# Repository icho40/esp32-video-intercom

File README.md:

# ESP32 Open Intercom

Lokale Video-Türsprechanlage für drei Parteien: Eine Türstation mit zwei ESP32-S3-Boards versorgt Android-Tablets mit Klingelmeldung, Livebild und Audio. Gegensprechen erfolgt über eine gedrückt gehaltene Sprechtaste. Für den Betrieb wird keine Cloud benötigt.

## Aufbau

**Beide ESP32-Boards sitzen zusammen mit der Steuerplatine im Gehäuse der Türstation.**

- **Seeed XIAO ESP32-S3 Sense:** erfasst Kamerabilder und Mikrofonton. Bild und Ton gehen über UART mit 2 Mbit/s zum Waveshare. Mikrofonaufnahme und Versand sind getrennt; Audio wird beim Senden bevorzugt.
- **Waveshare ESP32-S3 DevKit:** liest die drei Klingeltaster, verwaltet Ruf und Gespräch, überträgt die Daten im WLAN und empfängt die Sprache vom Tablet.
- **MAX98357A und Lautsprecher:** geben den vom Tablet gesendeten Ton an der Türstation aus. Der Rückweg läuft direkt vom Waveshare über I²S zum Verstärker.
- **Gemeinsame Steuerplatine:** verbindet die Komponenten und versorgt beide Boards über ihren 5-V/GND-Eingang.
- **Android-App auf drei Fire-Tablets:** P1 = Erdgeschoss, P2 = 1. Stock, P3 = Keller. Jedes Tablet reagiert auf seine zugewiesene Klingeltaste und verwendet seinen eigenen Klingelton. Fully Single App Kiosk übernimmt den Kioskbetrieb.

Ein Router beziehungsweise Access Point verbindet Türstation und Innenstationen. Die aktuellen Innenstationen verwenden die native Android-App; die älteren Browser-Oberflächen im Repository sind historische Entwicklungsstände.

## Funktionen

| Funktion | Stand |
|---|---|
| Drei Klingeltaster mit Zuordnung P1/P2/P3 | Implementiert |
| Livebild und Audio von der Türstation | Implementiert und bereits praktisch betrieben |
| Gegensprechen per Sprechtaste, Ende-Taste | In der Tablet-App implementiert und praktisch geprüft |
| Unbeantworteter Ruf endet nach 30 Sekunden | Implementiert |
| Gesprächsfreigabe nach Verbindungsabbruch | Implementiert |
| Eigene Klingeltöne und Etagenanzeige | Implementiert; P3 heißt Keller |
| Tablet-Autostart, Home-Sperre und Mikrofonfreigabe | Mit Fully eingerichtet und nach Neustart geprüft |
| WLAN-Empfangsanzeige über Zahnrad | Implementiert auf allen drei Tablets, ohne PIN |
| Gemeinsamer WLAN-Wechsel von Tablet und Türstation | Implementiert, mit Rückfall bei fehlender Bestätigung |
| RSSI-Anzeige und WLAN-Diagnoseseite | Implementiert |
| Firmware-Update des Waveshare über WLAN | Implementiert und am Gerät geprüft |
| Separate Handy-App für P1 im selben WLAN | Testversion; Sprechtastenprüfung noch offen |

**Aktuell offene Punkte:** Im zuletzt dokumentierten Standorttest vom 25.10.2026 bestand erneut eine Störung beim Kamera-/Audioempfang über UART. Die Diagnose zeigt diese an, behebt sie aber nicht. Ein erfolgreicher vollständiger Audio-/Videotest nach diesem Standortwechsel ist noch nicht dokumentiert. Die Handy-Testversion ist ebenfalls noch nicht abschließend freigegeben.

MQTT, Home Assistant und Türöffnersteuerung gehören nicht zum derzeit bestätigten Funktionsumfang.

## Gebrauchsanleitung

[Druckbare Anleitung als PDF](docs/Gebrauchsanleitung.pdf) · [Admin-Fassung mit Lautstärke](docs/Gebrauchsanleitung-Admin.pdf) | [Bearbeitbare Textfassung](docs/Gebrauchsanleitung.md) | Handy-Apps installieren: [PDF](docs/Handy-App-Installation.pdf) · [Text](docs/Handy-App-Installation.md)

## Bedienung

1. Klingeltaster P1, P2 oder P3 an der Türstation drücken.
2. Das zugewiesene Tablet klingelt und zeigt das Kamerabild.
3. **Sprechen gedrückt halten:** nimmt den Ruf an und aktiviert das Tablet-Mikrofon. Währenddessen ist die Wiedergabe der Türstation am Tablet stumm.
4. **Loslassen:** beendet die Mikrofonübertragung; der Ton der Türstation wird wieder hörbar.
5. **Ende:** beendet den Ruf. Ohne Annahme läuft er nach 30 Sekunden ab.

Bei der Einrichtung die Mikrofonabfrage **direkt am Tablet mit „Bei Nutzung der App“ bestätigen**. Eine ausschließlich über USB gesetzte Freigabe ersetzt diesen Schritt im bewährten Ablauf nicht.

## WLAN und Wartung

An jedem Tablet: **Zahnrad rechts oben antippen** öffnet direkt die **WLAN-Empfangsanzeige** der Türstation mit Signal, IP und Diagnoseseite. Seit 06.11.2026 ohne PIN und ohne Menüpunkt zum Ändern des WLANs.

Neue WLAN-Zugangsdaten bekommt die Station über ihr Einrichtungs-WLAN: Ist sie 60 Sekunden ohne WLAN, öffnet sie „OpenIntercom-Setup“ selbst. Mit einem Handy verbinden und http://192.168.4.1 öffnen. Hängt sie in einem WLAN, das die Tablets nicht erreichen, hilft nur ein Neustart mit Netzwahl (P1 = Test-WLAN, P2 = Haus-WLAN) oder USB; eine Haltegeste an P1 gibt es seit 06.11.2026 nicht mehr. Zugangsdaten werden auf der Station gespeichert; die aktuelle Firmware enthält kein fest eingebautes privates WLAN als Rückfall.

- Diagnose im lokalen Netz: http://STATIONS-IP/diagnose
- JSON-Diagnose: http://STATIONS-IP/api/diagnose
- Waveshare-Update: http://STATIONS-IP/update, mit Administrator-Anmeldung und Sitzungstoken
- OTA aktualisiert die Waveshare-Firmware; die XIAO wird separat per USB programmiert.

Details zu Freigaben, WLAN-Wechsel, Wiederherstellung und OTA: [WLAN-Einrichtung und Wartung](docs/wlan-einrichtung.md).

## Quellcode

| Verzeichnis | Zweck |
|---|---|
| firmware/doorstation_v2 | Aktuelle Waveshare-Firmware |
| firmware/xiao_cam/xiao_video_uart | XIAO: Kamera, Mikrofon und UART |
| android | Tablet-App |
| android-phone | Handy-Apps, je eine pro Klingel (P1–P3) |
| hardware/aussenstation | KiCad-Unterlagen der Steuerplatine |
| tools | Wartungswerkzeuge, unter anderem gedrosselter OTA-Upload |

Weitere technische Details: [Architektur](docs/ARCHITECTURE.md), [Stand 17.10.2026](docs/stand-2026-10-17.md), [Tablet-Bildausrichtung 24.10.2026](docs/stand-2026-10-24.md). Datierte Dokumente halten den jeweiligen damaligen Prüfstand fest.

## Bauen

Tablet-App im Verzeichnis android:

    ./gradlew :app:assembleDebug

Handy-Testversion im Verzeichnis android-phone:

    ./gradlew :app:assembleDebug

Waveshare mit Arduino CLI:

    arduino-cli compile --fqbn esp32:esp32:esp32s3:FlashSize=8M,PartitionScheme=default_8MB,PSRAM=opi,CDCOnBoot=default firmware/doorstation_v2

Die erforderlichen Arduino-Bibliotheken und das ESP32-Boardpaket müssen installiert sein. Für USB-Wiederherstellung nach OTA den aktiven Firmware-Slot berücksichtigen; nicht blind nur app0 überschreiben.

## Eigene Anpassungen

Diese öffentliche Fassung enthält keine Zugangsdaten und keine Medien Dritter. Vor dem Einsatz anpassen:

- **WLAN-Namen:** In `firmware/doorstation_v2/Config.h` stehen die Namen der beiden WLANs (`HOME_WIFI_SSID`, `TEST_WIFI_SSID`). Das Firmware-Update ist nur im `HOME_WIFI_SSID` erlaubt. Die Zugangsdaten selbst kommen über das Einrichtungs-WLAN in die Station.
- **Admin-Passwort** für `/update`, `/audio` und `/ansage`: per USB mit `OTA_SET_PASSWORD <passwort>` setzen. In der Anleitung steht dafür der Platzhalter ‹Admin-Passwort›.
- **Klingeltöne:** `tools/make_ringtones.py` erzeugt einfache, freie Töne (`res/raw/klingel_p1.mp3` … `p3`). Eigene Töne unter gleichem Namen ersetzen.
- **Logo:** optional. Eine eigene PNG-Datei als `android/app/src/main/res/drawable-nodpi/wg_logo.png` ablegen, dann erscheint sie im Kopf der PDF-Anleitung. In den Apps ist kein Logo eingebaut.
- **Platzhalter** wie `[Seriennr. Tablet 1]` oder `XX:XX:XX:XX:XX:XX` in den datierten Stand-Dokumenten stehen für die Geräte der ursprünglichen Installation.

Fertige Firmware und APKs gibt es unter **Releases**.

**Sprachaufnahmen:** Die beiden voreingestellten Ansagesätze (`Sprache/nicht_da_andere_etage.mp3`, `Sprache/nicht_zuhause_auf_dem_handy_erreichbar.mp3`, eingebaut in `firmware/doorstation_v2/DefaultAnnouncements.h`) wurden mit ElevenLabs im bezahlten Starter-Tarif erzeugt, der die kommerzielle Nutzung erlaubt. Wer eigene Sätze verwenden will, ersetzt die Dateien und führt `tools/make_default_announcements.py` aus oder lädt Sätze über die Seite `/ansage` hoch.

## Projektstatus und Lizenz

Eigenbauprojekt, seit November 2026 an einem Haus mit drei Parteien in Betrieb. Die dokumentierten Tests unterscheiden zwischen bereits bestätigten Funktionen und noch offenen Prüfungen. Private WLAN-Zugangsdaten, PINs, OTA-Passwörter und Geräteabbilder gehören nicht ins Repository.

GPL-3.0-or-later, siehe [Lizenz](LICENSE).

Dokumentation aktualisiert am 23.11.2026.

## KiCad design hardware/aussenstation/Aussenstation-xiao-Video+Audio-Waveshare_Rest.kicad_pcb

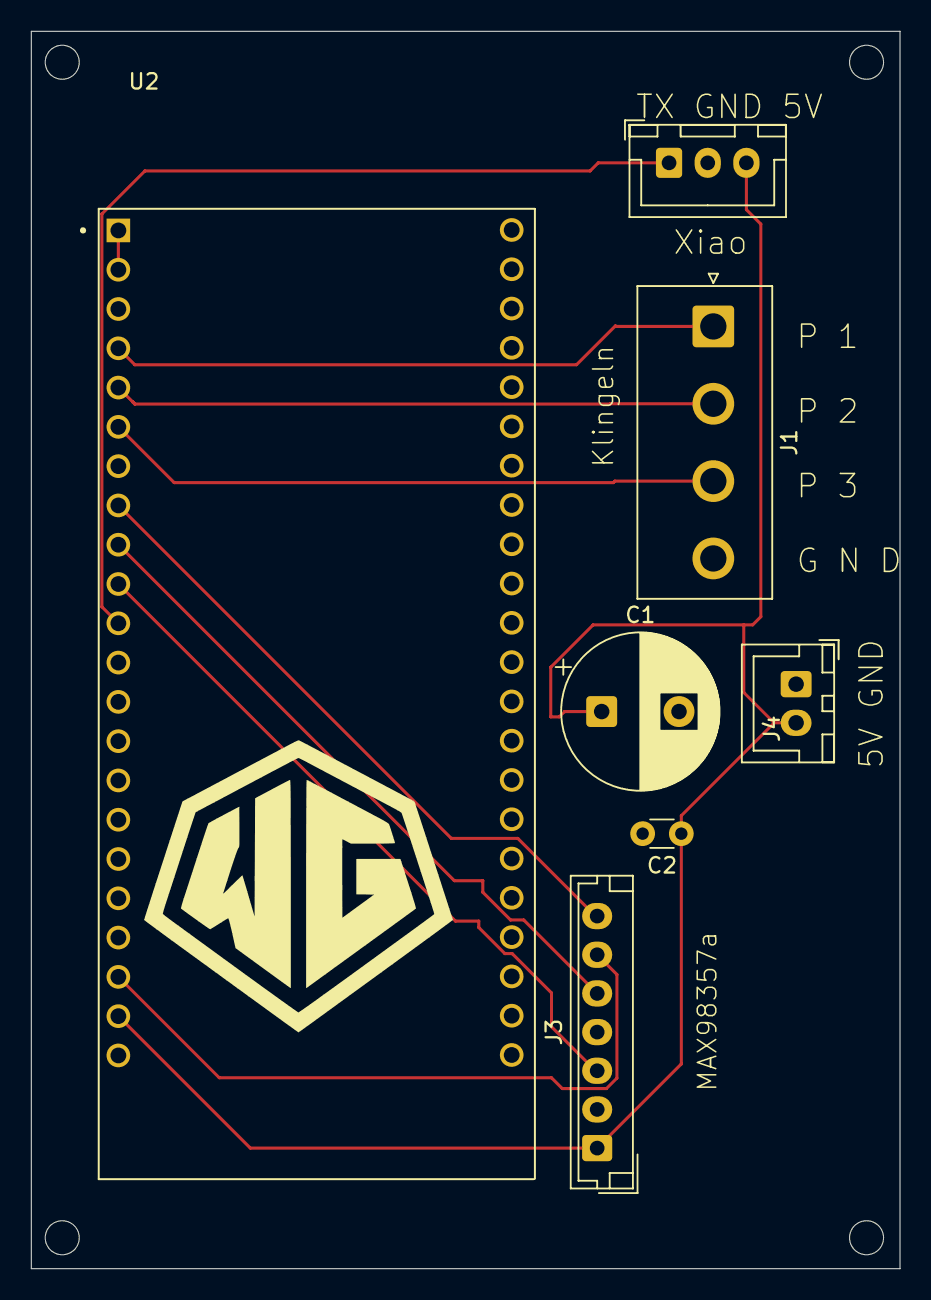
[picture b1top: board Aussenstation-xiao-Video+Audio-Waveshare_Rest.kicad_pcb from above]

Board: 2 copper layers, 56.2 x 80.0 mm, 7 parts (0 on the bottom side), 11 nets.

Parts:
C1: C_Polarized_Small; CP_Radial_D10.0mm_P5.00mm
C2: C_Small; C_Disc_D3.0mm_W1.6mm_P2.50mm
J1: Klingeln; JST_NV_B04P-NV_1x04_P5.00mm_Vertical
J2: Anschluß Xiao; JST_XH_B3B-XH-A_1x03_P2.50mm_Vertical
J3: MAX98357a; JST_EH_B7B-EH-A_1x07_P2.50mm_Vertical
J4: 5V; JST_XH_B2B-XH-A_1x02_P2.50mm_Vertical
U2: ESP32-S3-DEVKITC-1-N8R2; XCVR_ESP32-S3-DEVKITC-1-N8R2

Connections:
3V3: U2.J1_1 (3V3), U2.J1_2 (3V3)
GND: C1.2, C2.2, J1.4, J2.2, J3.2, J4.1 (GND), U2.J1_22 (GND), U2.J3_1 (GND), U2.J3_21 (GND), U2.J3_22 (GND)
unnamed: J1.1, U2.J1_4 (GPIO4)
unnamed: J1.2, U2.J1_5 (GPIO5)
unnamed: J1.3, U2.J1_6 (GPIO6)
unnamed: J2.1, U2.J1_11 (GPIO18)
unnamed: C1.1, C2.1, J2.3, J3.1, J4.2 (5V), U2.J1_21 (5V0)
unnamed: J3.3, U2.J1_10 (GPIO17)
unnamed: J3.5, U2.J1_9 (GPIO16)
unnamed: J3.6, U2.J1_20 (GPIO14)
unnamed: J3.7, U2.J1_8 (GPIO15)
